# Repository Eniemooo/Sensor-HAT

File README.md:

# Sensor HAT v3 "Universal"

*Deutsch (ausführliche Anleitung): [README.de.md](README.de.md)*

An open-hardware indoor-environment sensor board, designed in KiCad 10 (65 × 56 mm, 4 layers). It runs in one of two modes, **never both at once**:

1. **HAT for Raspberry Pi** 2, 3, 4 and 5, with a HAT+ ID EEPROM and Python.
2. **Standalone** with a plug-in **Seeed Studio XIAO ESP32-S3, -C3 or -C6** (not included). It is powered over the XIAO's USB-C, runs ESPHome and shows up in Home Assistant.

> **Status:** the design is complete. KiCad ERC and DRC report no errors, and the ESPHome configs validate. **It has not been tested in hardware yet.** Build prototypes before ordering in quantity.

## What is on the board

| Function | Part | I²C address / Pi GPIO / XIAO pin |
|---|---|---|
| CO₂ (photoacoustic, not an eCO₂ estimate) | Sensirion SCD41, own 3.3 V regulator | 0x62 |
| Temperature, humidity | Sensirion SHT40 on a milled, thermally isolated island | 0x44 |
| VOC and NOx index | Sensirion SGP41 | 0x59 |
| Ambient light (lux) | Vishay VEML7700 | 0x10 |
| Sound level | TDK ICS-43434 I²S microphone | Pi GPIO18/19/20, XIAO D1/D0/D2 |
| RGB status LED (e.g. CO₂ traffic light) | WS2812B-2020 with 5 V level shifter | Pi GPIO10, XIAO D10 |
| Button | SW1 | Pi GPIO27, XIAO D4 |
| Buzzer (passive, 4 kHz) | MLT-5020 | Pi GPIO13, XIAO D3 |
| Particulate sensor port (Sensirion SEN6x/SEN5x) | J4, JST GH 6-pin, own regulator | 0x6B / 0x69 |
| mmWave radar / UART (e.g. HLK-LD2420; LD2410C with 5 V and a re-ordered cable) | J3 | Pi GPIO14/15 (+GPIO17 OUT), XIAO D6/D7 |
| 1-Wire (e.g. DS18B20) | J2 | Pi GPIO4, XIAO D5 (JP6) |
| Qwiic / STEMMA QT | J5, JST SH 4-pin | I²C, 3.3 V |
| Spare GPIOs (Pi only) | J6, 2×5 pads, not populated | GPIO5, 12, 22–26 |
| HAT ID EEPROM | onsemi CAT24C32 | ID_SD/ID_SC, 0x50 |

All parts are in active production. The one exception is the ICS-43434 microphone: it is obsolete but still widely stocked.

Two LM66100 ideal diodes keep the two power sources apart, so no current flows from the Pi into the XIAO's USB port or the other way round.

## Using it

### XIAO mode (ESPHome / Home Assistant)

1. Copy the files for your XIAO from [`software/esphome/`](software/esphome/): `sensor-hat-xiao-s3.yaml`, `-c3.yaml` or `-c6.yaml`. You always need `sensor-hat-common.yaml` and a `secrets.yaml` as well. Start from `secrets.yaml.example` and fill in:
   - your Wi-Fi name and password
   - an API encryption key (`openssl rand -base64 32`), which also protects OTA updates
   - a password for the fallback hotspot (at least 8 characters)

   The placeholders in the template are rejected by `esphome config` on purpose. With more than one board, give each its own `name:` in the substitutions, for example `sensor-hat-kitchen`.
2. Flash the XIAO once over USB **without the board attached**. Then plug it into J7/J8 with the USB-C facing outwards. Later updates go over Wi-Fi. When you add the device in Home Assistant, it asks for the API encryption key.
3. Calibrate the readings:
   - set `altitude_compensation` to your altitude
   - after 15 minutes of running, enter the SHT40 `offset` against a reference thermometer

Notes:
- **Power supply:** at least 5 V / 1.5 A with the particulate sensor and radar connected, otherwise at least 1 A. A PC USB port is not enough.
- **Battery:** do not connect a battery to the XIAO.
- **Antenna:** use a U.FL antenna. This also applies to the C6: its chip antenna sits 11 mm above the ground plane. On the C6, also set `restore_mode: ALWAYS_ON` for the `antenna_select` switch in `sensor-hat-xiao-c6.yaml` (GPIO14 high selects the U.FL socket).
- **Strapping-pin warnings:** ESPHome warns about strapping pins on the C3 (GPIO2/8/9) and the S3 (GPIO3). These pins are pulled up or not sampled on this board, so the warnings are expected and harmless.

### Raspberry Pi mode

1. Leave the XIAO socket empty.
2. Add the lines from [`software/config.txt.snippet`](software/config.txt.snippet) to `/boot/firmware/config.txt` and reboot.
3. Run [`software/sensor_test.py`](software/sensor_test.py). The pip packages it needs are listed at the top of the file.
4. To program the HAT+ ID EEPROM, see [`software/eeprom_settings.txt`](software/eeprom_settings.txt) and the German README.

### Solder jumpers: check them before you connect anything

| Jumper | As delivered | Function |
|---|---|---|
| JP1 / JP3 | open | J3 supply: JP1 = 3.3 V, JP3 = 5 V. **Never bridge both.** |
| JP4 / JP5 | JP4 closed | J4 supply: JP4 = 3.3 V for SEN6x, JP5 = 5 V for SEN5x. **5 V destroys a SEN6x.** Cut JP4, check with a multimeter that it is open, then bridge JP5. |
| JP6 | 1-2 closed | XIAO D5 = 1-Wire (J2). For the radar OUT pin, cut 1-2 and bridge 2-3. |
| JP2 | open | Bridge it to make the HAT EEPROM writable (Pi only). |

- **J3 radar:** the pin order is V+, GND, module TX, module RX, OUT.
  - HLK-LD2420 and LD2410S fit directly (bridge JP1, 3.3 V).
  - LD2410C and LD2450 need JP3 (5 V) and a re-ordered cable.
  - In ESPHome, use `sensor-hat-radar-ld2410.yaml` for the LD2410/LD2410C and the `ld2420` component for the LD2420. ESPHome has no UART support for the LD2410S, so only its OUT pin works (JP6 2-3).
- **J4 particulate sensor:** use a 6-pin JST GH cable wired pin 1 to pin 1 (VDD).
  - Check the cable with a multimeter first: crossed cables exist.
  - In XIAO mode use a SEN6x. A SEN5x needs at least 4.5 V, which is marginal on USB power.

## Ordering

[`production/`](production/) holds JLCPCB files: Gerber zip, BOM and CPL in two variants. The "komplett" variant also has JLCPCB solder the through-hole headers and XIAO sockets. The 40-pin Pi socket J1 is always soldered by hand.

Recommended settings:
- 4 layers, 1.6 mm, ENIG
- Standard PCBA, top side only, peak 245 °C
- tooling holes added by JLCPCB. The board (65 × 56 mm) is smaller than the 70 × 70 mm Standard-PCBA minimum, so it needs edge rails: on the left and right edges and one on the top edge (about 75 × 70 mm in total), never on the bottom edge with the milled sensor island. Have JLCPCB confirm this.
- **no board washing**

The complete order remark is in the German README, section "Bei JLCPCB bestellen".

Estimated landed cost per assembled board for the SMD-only variant, incl. 19 % German VAT. You buy and solder the headers J1–J3, J7 and J8 yourself. `python3 -I scripts/cost.py` recalculates it with live part prices:

| Boards | 2 | 5 | 20 | 50 | 100 |
|---|---|---|---|---|---|
| per board | ~125 € | ~77 € | ~50 € | ~42 € | ~37 € |

Small orders are expensive because of fixed setup fees, so a community group buy at cost is planned (German: [`docs/Sammelbestellung.md`](docs/Sammelbestellung.md)).

## Repository layout

| Path | Contents |
|---|---|
| `Sensor-HAT.kicad_pro/.kicad_sch/.kicad_pcb` | KiCad 10 project |
| `production/` | Gerber, BOM, CPL for JLCPCB |
| `docs/` | schematic and assembly PDFs, renders, group-buy documents (German) |
| `software/` | ESPHome configs, Pi config, test script, EEPROM settings |
| `lib/` | project symbols and footprints (3D models: see below) |
| `scripts/` | the generator: `design.py` (parts and nets) and `placement.py` are the single source of truth; `build.sh` regenerates schematic and board and autoroutes them |

## Building from source

```bash
pip install easyeda2kicad
python3 -I scripts/fetch_3d_models.py .   # LCSC 3D models, only needed for 3D view, renders, STEP
export FREEROUTING_JAR=/path/to/freerouting-2.5.0.jar
scripts/build.sh                          # schematic + ERC, board, autorouting, GND repair, DRC
python3 -I scripts/export.py .            # Gerber, BOM, CPL, PDFs, renders, STEP
```

Requirements:
- KiCad 10
- Java
- [Freerouting](https://github.com/freerouting/freerouting) 2.5

The scripts expect KiCad on macOS at `~/Applications/KiCad/KiCad.app`. For other installations, change the paths at the top of `build.sh`, `kicadlib.py`, `gen_pcb.py`, `route.py`, `cleanup.py` and `export.py`. If your Java is not Homebrew's openjdk, run `export JAVA=$(which java)` before `build.sh`.

## Licence

- Hardware (KiCad project, `scripts/design.py` and `scripts/placement.py`, production files, PDFs, renders): [CERN-OHL-S-2.0](LICENSES/CERN-OHL-S-2.0.txt)
- Software and the other scripts: [MIT](LICENSES/MIT.txt)
- Documentation: [CC-BY-SA-4.0](LICENSES/CC-BY-SA-4.0.txt) or, at your choice, [CERN-OHL-S-2.0](LICENSES/CERN-OHL-S-2.0.txt)

Source: <https://github.com/Eniemooo/Sensor-HAT>. Which licence covers which file is listed in [LICENSE.md](LICENSE.md). Some symbols and footprints come from the LCSC/EasyEDA library, which has no licence of its own. These parts, and the trademarks, are listed in [NOTICE.md](NOTICE.md).

Raspberry Pi is a trademark of Raspberry Pi Ltd. This project is not affiliated with Raspberry Pi Ltd or Seeed Studio. No warranty.

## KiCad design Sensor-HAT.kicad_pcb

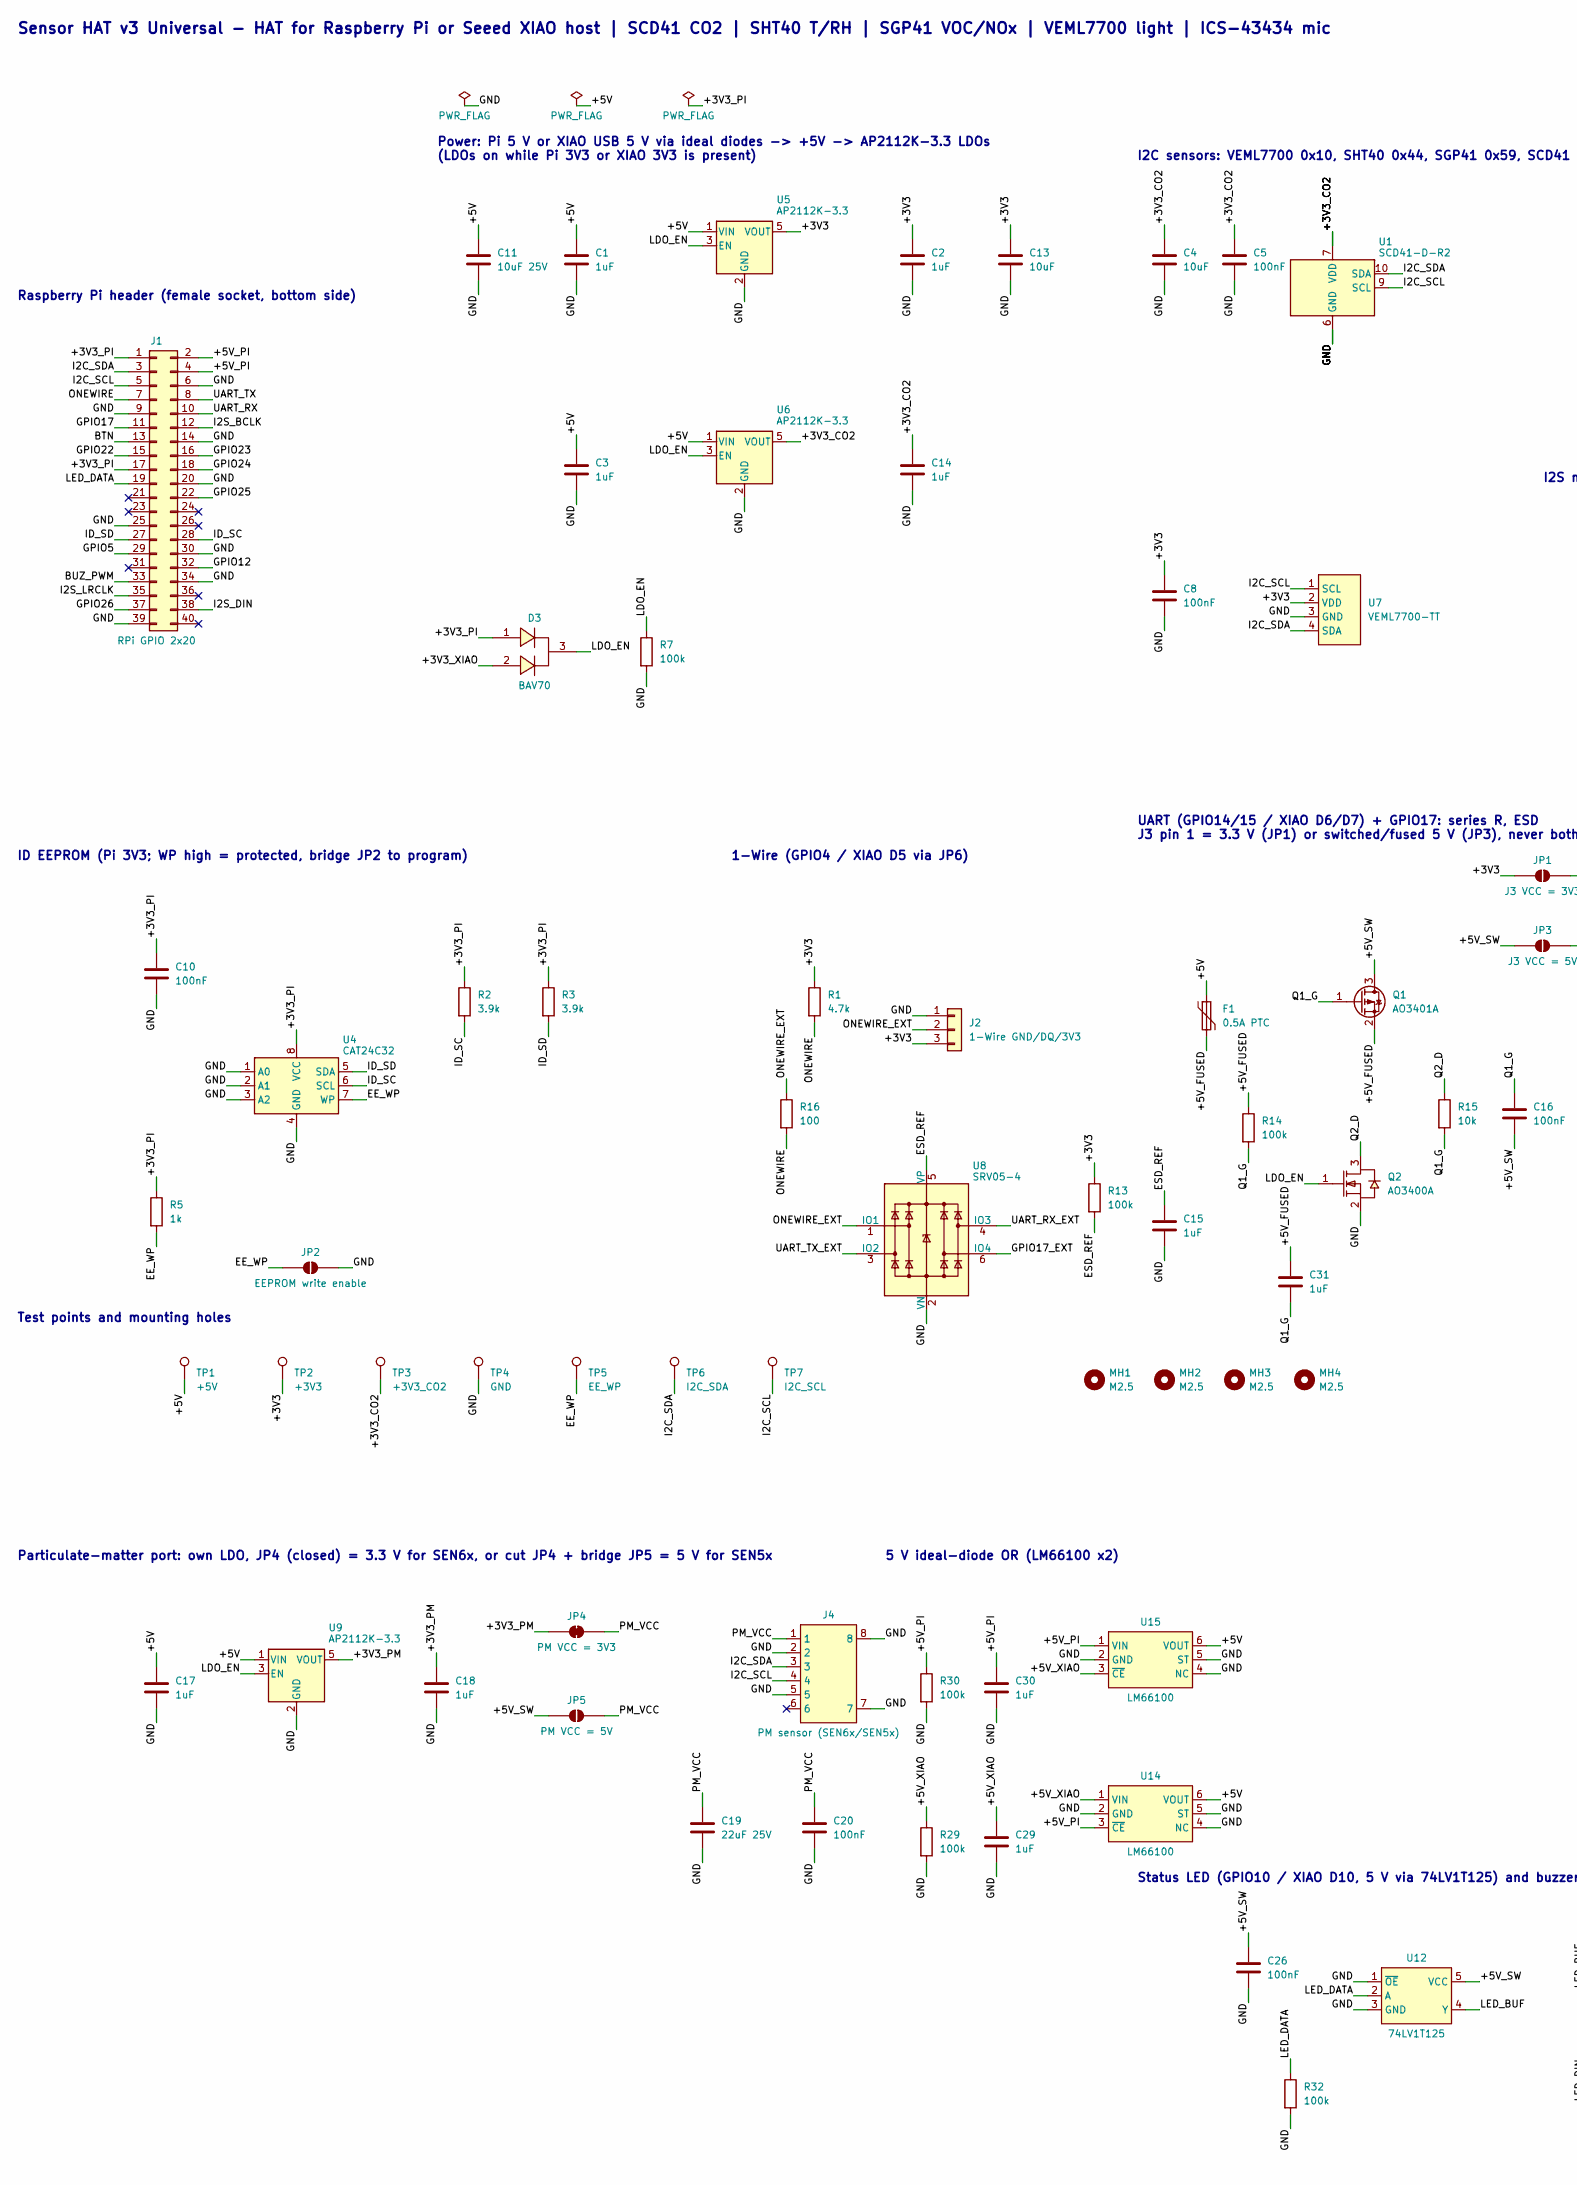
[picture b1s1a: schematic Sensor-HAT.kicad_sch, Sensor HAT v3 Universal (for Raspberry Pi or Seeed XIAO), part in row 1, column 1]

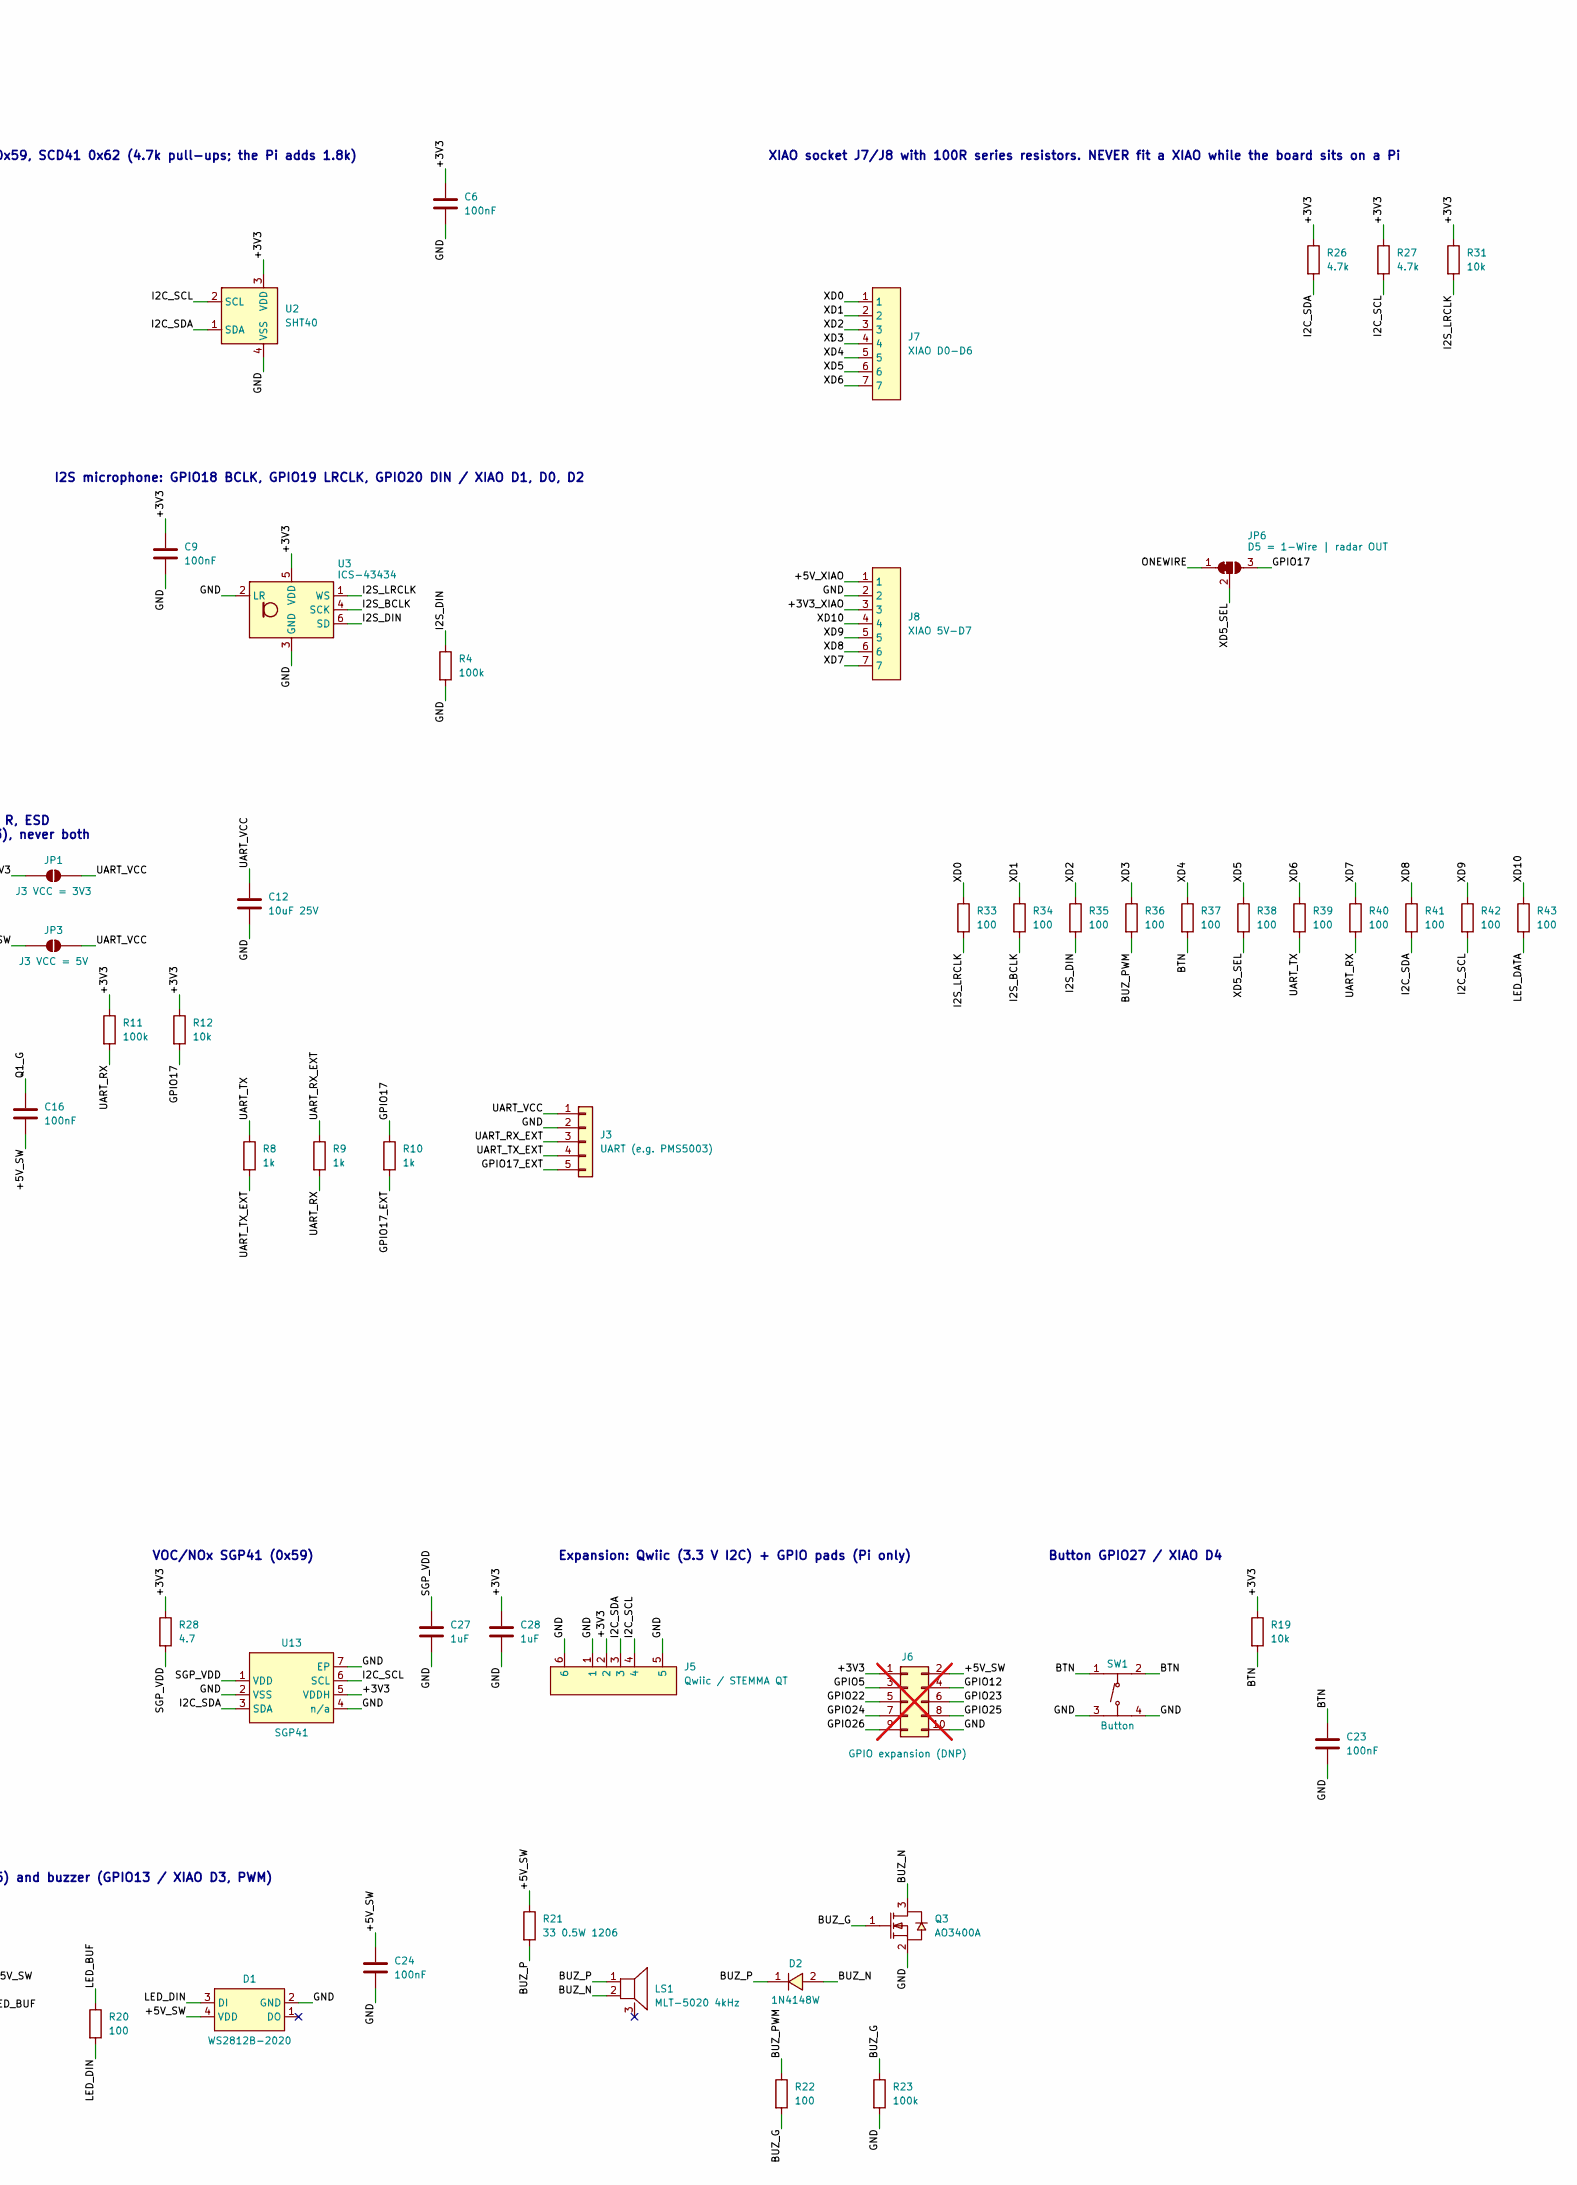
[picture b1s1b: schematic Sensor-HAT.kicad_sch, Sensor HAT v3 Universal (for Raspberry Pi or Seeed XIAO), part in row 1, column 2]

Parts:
C1, C2, C3, C14, C15, C17, C18, C27, C28, C29, C30, C31: 1uF; C_0603_1608Metric; MPN CL10A105KB8NNNC; LCSC C15849
C4, C13: 10uF; C_0603_1608Metric; MPN CL10A106KP8NNNC; LCSC C19702
C5, C6, C8, C9, C10, C16, C20, C23, C24, C26: 100nF; C_0603_1608Metric; MPN CC0603KRX7R9BB104; LCSC C14663
C11, C12: 10uF 25V; C_0805_2012Metric; MPN CL21A106KAYNNNE; LCSC C15850
C19: 22uF 25V; C_0805_2012Metric; MPN CL21A226MAQNNNE; LCSC C45783
D1: WS2812B-2020; LED-SMD_4P-L2.2-W2.0-P1.00_WS2815C-2020-4P; MPN WS2812B-2020-V6; LCSC C52917434
D2: 1N4148W; SOD-123F_L2.7-W1.6-LS3.8-RD; MPN 1N4148W; LCSC C81598
D3: BAV70; SOT-23-3_L3.0-W1.7-P0.95-LS2.9-BR; MPN BAV70; LCSC C68978
F1: 0.5A PTC; Fuse_1206_3216Metric; MPN nSMD050-33V; LCSC C70077
J1: RPi GPIO 2x20; PinSocket_2x20_P2.54mm_Vertical; MPN 2.54-2*20; LCSC C2977589
J2: 1-Wire GND/DQ/3V3; PinHeader_1x03_P2.54mm_Vertical; MPN 2.54-1*3P; LCSC C49257
J3: UART (e.g. PMS5003); PinHeader_1x05_P2.54mm_Vertical; MPN HX PZ2.54-1x5P ZZ; LCSC C32713271
J4: PM sensor (SEN6x/SEN5x); CONN-SMD_6P-P1.25_BM06B-GHS-TBT-LF-SN-N; MPN BM06B-GHS-TBT(LF)(SN); LCSC C189892
J5: Qwiic / STEMMA QT; CONN-SMD_BM04B-SRSS-TB; MPN BM04B-SRSS-TB(LF)(SN); LCSC C160390
J6: GPIO expansion (DNP); PinHeader_2x05_P2.54mm_Vertical; not fitted
J7: XIAO D0-D6; HDR-TH_7P-P2.54-V-F; MPN PM254-1-07-Z-8.5; LCSC C2897370
J8: XIAO 5V-D7; HDR-TH_7P-P2.54-V-F; MPN PM254-1-07-Z-8.5; LCSC C2897370
JP1: J3 VCC = 3V3; SolderJumper-2_P1.3mm_Open_RoundedPad1.0x1.5mm
JP2: EEPROM write enable; SolderJumper-2_P1.3mm_Open_RoundedPad1.0x1.5mm
JP3: J3 VCC = 5V; SolderJumper-2_P1.3mm_Open_RoundedPad1.0x1.5mm
JP4: PM VCC = 3V3; SolderJumper-2_P1.3mm_Bridged_RoundedPad1.0x1.5mm
JP5: PM VCC = 5V; SolderJumper-2_P1.3mm_Open_RoundedPad1.0x1.5mm
JP6: D5 = 1-Wire | radar OUT; SolderJumper-3_P1.3mm_Bridged12_RoundedPad1.0x1.5mm
LS1: MLT-5020 4kHz; BUZ-SMD_L5.0-W5.5-P4.60; MPN MLT-5020; LCSC C94598
MH1, MH2, MH3, MH4: M2.5; MountingHole_2.7mm_M2.5
Q1: AO3401A; SOT-23_L2.9-W1.3-P1.90-LS2.4-BR; MPN AO3401A; LCSC C15127
Q2, Q3: AO3400A; SOT-23_L2.9-W1.3-P1.90-LS2.4-BR; MPN AO3400A; LCSC C20917
R1, R26, R27: 4.7k; R_0603_1608Metric; MPN 0603WAF4701T5E; LCSC C23162
R2, R3: 3.9k; R_0603_1608Metric; MPN 0603WAF3901T5E; LCSC C23018
R4, R7, R11, R13, R14, R23, R29, R30, R32: 100k; R_0603_1608Metric; MPN 0603WAF1003T5E; LCSC C25803
R5, R8, R9, R10: 1k; R_0603_1608Metric; MPN 0603WAF1001T5E; LCSC C21190
R12, R15, R19, R31: 10k; R_0603_1608Metric; MPN 0603WAF1002T5E; LCSC C25804
R16, R20, R22, R33, R34, R35, R36, R37, R38, R39, R40, R41, R42, R43: 100; R_0603_1608Metric; MPN 0603WAF1000T5E; LCSC C22775
R21: 33 0.5W 1206; R_1206_3216Metric; MPN FRP1206F33R0TS; LCSC C5713420
R28: 4.7; R_0603_1608Metric; MPN 0603WAF470KT5E; LCSC C23164
SW1: Button; SW-SMD_4P-L5.1-W5.1-P3.70-LS6.5-TL_H1.5; MPN TS-1187A-B-A-B; LCSC C318884
TP1: +5V; TestPoint_Pad_D1.5mm
TP2: +3V3; TestPoint_Pad_D1.5mm
TP3: +3V3_CO2; TestPoint_Pad_D1.5mm
TP4: GND; TestPoint_Pad_D1.5mm
TP5: EE_WP; TestPoint_Pad_D1.5mm
TP6: I2C_SDA; TestPoint_Pad_D1.5mm
TP7: I2C_SCL; TestPoint_Pad_D1.5mm
U1: SCD41-D-R2; LGA-20_L10.1-W10.1-P1.25-TL_SCD41-D-R2; MPN SCD41-D-R2; LCSC C3659294
U2: SHT40; SHT4x_DFN-4_1.5x1.5mm_P0.8mm_NoCentralPad; MPN SHT40-AD1B-R2; LCSC C2909890
U3: ICS-43434; InvenSense_ICS-43434-6_3.5x2.65mm; MPN ICS-43434; LCSC C5656610
U4: CAT24C32; SOIC-8_L5.0-W4.0-P1.27-LS6.0-BL; MPN CAT24C32WI-GT3; LCSC C81193
U5, U6, U9: AP2112K-3.3; SOT-25-5_L2.9-W1.6-P0.95-LS2.8-BL; MPN AP2112K-3.3TRG1; LCSC C51118
U7: VEML7700-TT; SENSOR-SMD_EML7700-TT; MPN VEML7700-TT; LCSC C1850416
U8: SRV05-4; SOT-23-6_L2.9-W1.6-P0.95-LS2.8-BR; MPN SRV05-4-P-T7; LCSC C85364
U12: 74LV1T125; SOT-23-5_L3.0-W1.7-P0.95-LS2.8-BL; MPN SN74LV1T125DBVR; LCSC C473338
U13: SGP41; DFN-6_L2.4-W2.4-P0.80-TL-EP; MPN SGP41-D-R4; LCSC C3659325
U14, U15: LM66100; SC-70-6_L2.0-W1.3-P0.65-LS2.1-BL; MPN LM66100DCKR; LCSC C2869734

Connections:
/+3V3: C2.1, C6.1, C8.1, C9.1, C13.1, C28.1, J2.3, J5.2, J6.1, JP1.1 (A), R1.1, R11.1, R12.1, R13.1, R19.1, R26.1, R27.1, R28.1, R31.1, TP2.1, U2.3 (VDD), U3.5 (VDD), U5.5 (VOUT), U7.2 (VDD), U13.5 (VDDH)
/+3V3_CO2: C4.1, C5.1, C14.1, TP3.1, U1.7 (VDD), U1.19 (VDD), U6.5 (VOUT)
/+3V3_PI: C10.1, D3.1, J1.1, J1.17, R2.1, R3.1, R5.1, U4.8 (VCC)
/+3V3_PM: C18.1, JP4.1 (A), U9.5 (VOUT)
/+3V3_XIAO: D3.2, J8.3
/+5V: C1.1, C3.1, C11.1, C17.1, F1.1, TP1.1, U5.1 (VIN), U6.1 (VIN), U9.1 (VIN), U14.6 (VOUT), U15.6 (VOUT)
/+5V_FUSED: C31.1, F1.2, Q1.2 (S), R14.1
/+5V_PI: C30.1, J1.2, J1.4, R30.1, U14.3 (~CE), U15.1 (VIN)
/+5V_SW: C16.2, C24.1, C26.1, D1.4 (VDD), J6.2, JP3.1 (A), JP5.1 (A), Q1.3 (D), R21.1, U12.5 (VCC)
/+5V_XIAO: C29.1, J8.1, R29.1, U14.1 (VIN), U15.3 (~CE)
/BTN: C23.1, J1.13, R19.2, R37.2, SW1.1 (A), SW1.2 (B)
/BUZ_G: Q3.1 (G), R22.2, R23.1
/BUZ_N: D2.2 (A), LS1.2 (-), Q3.3 (D)
/BUZ_P: D2.1 (K), LS1.1 (+), R21.2
/BUZ_PWM: J1.33, R22.1, R36.2
/EE_WP: JP2.1 (A), R5.2, TP5.1, U4.7 (WP)
/ESD_REF: C15.1, R13.2, U8.5 (VP)
/GND: C1.2, C2.2, C3.2, C4.2, C5.2, C6.2, C8.2, C9.2, C10.2, C11.2, C12.2, C13.2, C14.2, C15.2, C17.2, C18.2, C19.2, C20.2, C23.2, C24.2, C26.2, C27.2, C28.2, C29.2, C30.2, D1.2 (GND), J1.6, J1.9, J1.14, J1.20, J1.25, J1.30, J1.34, J1.39, J2.1, J3.2, J4.2, J4.5, J4.7, J4.8, J5.1, J5.5, J5.6, J6.10, J8.2, JP2.2 (B), Q2.2 (S), Q3.2 (S), R4.2, R7.2, R23.2, R29.2, R30.2, R32.2, SW1.3 (C), SW1.4 (D), TP4.1, U1.6 (GND), U1.20 (GND), U1.21 (GND), U2.4 (VSS), U3.2 (LR), U3.3 (GND), U4.1 (A0), U4.2 (A1), U4.3 (A2), U4.4 (GND), U5.2 (GND), U6.2 (GND), U7.3 (GND), U8.2 (VN), U9.2 (GND), U12.1 (~OE), U12.3 (GND), U13.2 (VSS), U13.4 (n/a), U13.7 (EP), U14.2 (GND), U14.4 (NC), U14.5 (ST), U15.2 (GND), U15.4 (NC), U15.5 (ST)
/GPIO5: J1.29, J6.3
/GPIO12: J1.32, J6.4
/GPIO17: J1.11, JP6.3 (B), R10.1, R12.2
/GPIO17_EXT: J3.5, R10.2, U8.6 (IO4)
/GPIO22: J1.15, J6.5
/GPIO23: J1.16, J6.6
/GPIO24: J1.18, J6.7
/GPIO25: J1.22, J6.8
/GPIO26: J1.37, J6.9
/I2C_SCL: J1.5, J4.4, J5.4, R27.2, R42.2, TP7.1, U1.9 (SCL), U2.2 (SCL), U7.1 (SCL), U13.6 (SCL)
/I2C_SDA: J1.3, J4.3, J5.3, R26.2, R41.2, TP6.1, U1.10 (SDA), U2.1 (SDA), U7.4 (SDA), U13.3 (SDA)
/I2S_BCLK: J1.12, R34.2, U3.4 (SCK)
/I2S_DIN: J1.38, R4.1, R35.2, U3.6 (SD)
/I2S_LRCLK: J1.35, R31.2, R33.2, U3.1 (WS)
/ID_SC: J1.28, R2.2, U4.6 (SCL)
/ID_SD: J1.27, R3.2, U4.5 (SDA)
/LDO_EN: D3.3, Q2.1 (G), R7.1, U5.3 (EN), U6.3 (EN), U9.3 (EN)
/LED_BUF: R20.1, U12.4 (Y)
/LED_DATA: J1.19, R32.1, R43.2, U12.2 (A)
/LED_DIN: D1.3 (DI), R20.2
/ONEWIRE: J1.7, JP6.1 (A), R1.2, R16.2
/ONEWIRE_EXT: J2.2, R16.1, U8.1 (IO1)
/PM_VCC: C19.1, C20.1, J4.1, JP4.2 (B), JP5.2 (B)
/Q1_G: C16.1, C31.2, Q1.1 (G), R14.2, R15.2
/Q2_D: Q2.3 (D), R15.1
/SGP_VDD: C27.1, R28.2, U13.1 (VDD)
/UART_RX: J1.10, R9.2, R11.2, R40.2
/UART_RX_EXT: J3.3, R9.1, U8.4 (IO3)
/UART_TX: J1.8, R8.1, R39.2
/UART_TX_EXT: J3.4, R8.2, U8.3 (IO2)
/UART_VCC: C12.1, J3.1, JP1.2 (B), JP3.2 (B)
/XD0: J7.1, R33.1
/XD1: J7.2, R34.1
/XD2: J7.3, R35.1
/XD3: J7.4, R36.1
/XD4: J7.5, R37.1
/XD5: J7.6, R38.1
/XD5_SEL: JP6.2 (C), R38.2
/XD6: J7.7, R39.1
/XD7: J8.7, R40.1
/XD8: J8.6, R41.1
/XD9: J8.5, R42.1
/XD10: J8.4, R43.1

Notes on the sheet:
Sensor HAT v3 Universal - HAT for Raspberry Pi or Seeed XIAO host | SCD41 CO2 | SHT40 T/RH | SGP41 VOC/NOx | VEML7700 light | ICS-43434 mic
Raspberry Pi header (female socket, bottom side)
Power: Pi 5 V or XIAO USB 5 V via ideal diodes -> +5V -> AP2112K-3.3 LDOs
(LDOs on while Pi 3V3 or XIAO 3V3 is present)
I2C sensors: VEML7700 0x10, SHT40 0x44, SGP41 0x59, SCD41 0x62 (4.7k pull-ups; the Pi adds 1.8k)
I2S microphone: GPIO18 BCLK, GPIO19 LRCLK, GPIO20 DIN / XIAO D1, D0, D2
XIAO socket J7/J8 with 100R series resistors. NEVER fit a XIAO while the board sits on a Pi
ID EEPROM (Pi 3V3; WP high = protected, bridge JP2 to program)
1-Wire (GPIO4 / XIAO D5 via JP6)
UART (GPIO14/15 / XIAO D6/D7) + GPIO17: series R, ESD
J3 pin 1 = 3.3 V (JP1) or switched/fused 5 V (JP3), never both
Test points and mounting holes
Particulate-matter port: own LDO, JP4 (closed) = 3.3 V for SEN6x, or cut JP4 + bridge JP5 = 5 V for SEN5x
5 V ideal-diode OR (LM66100 x2)
VOC/NOx SGP41 (0x59)
Expansion: Qwiic (3.3 V I2C) + GPIO pads (Pi only)
Button GPIO27 / XIAO D4
Status LED (GPIO10 / XIAO D10, 5 V via 74LV1T125) and buzzer (GPIO13 / XIAO D3, PWM)

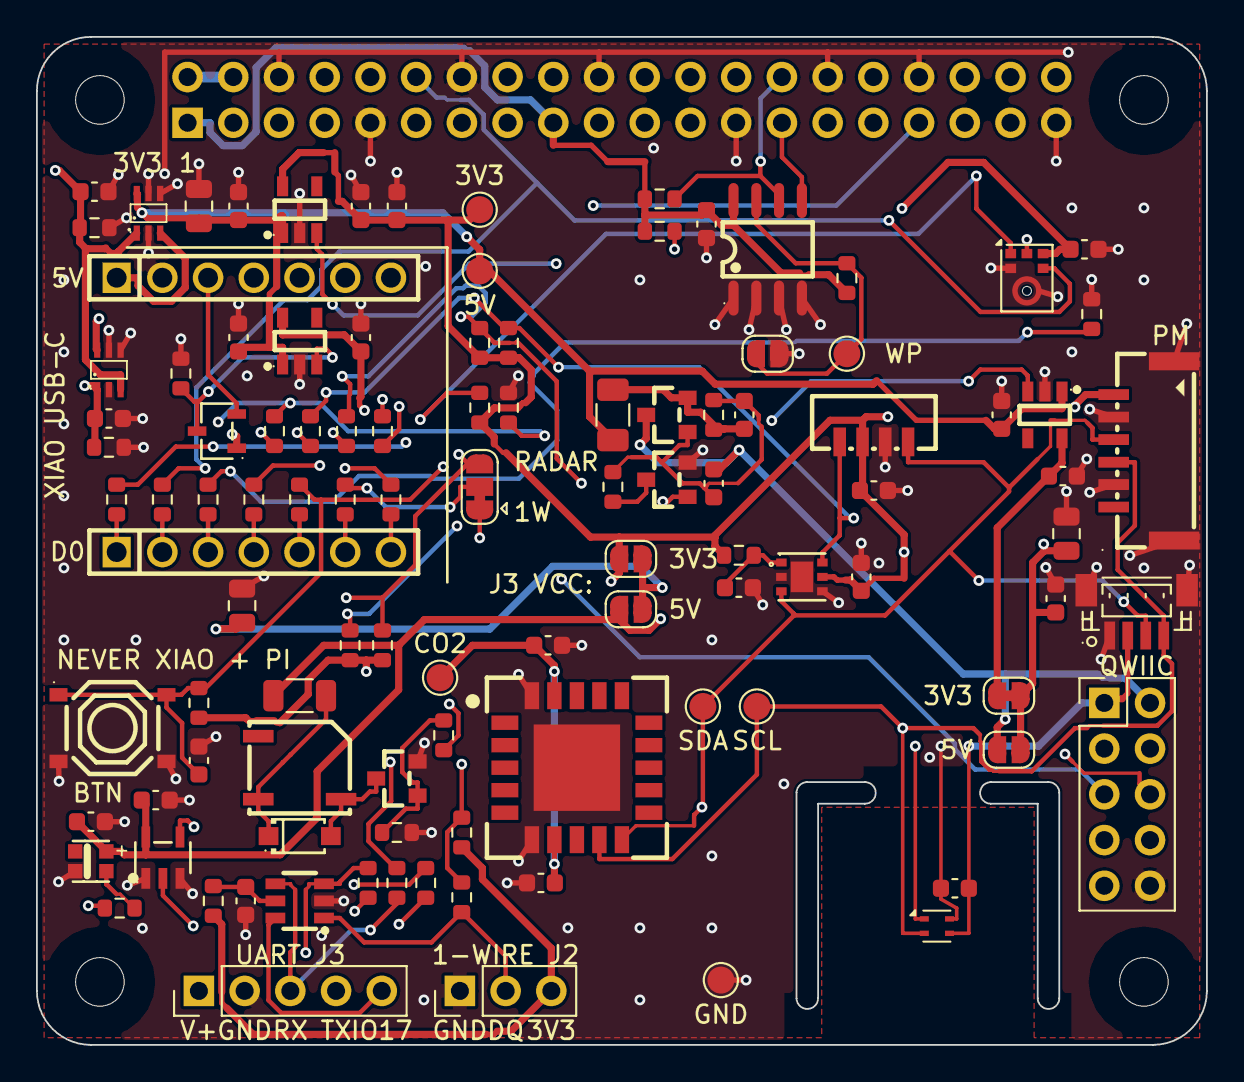
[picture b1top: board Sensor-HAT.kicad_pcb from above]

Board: 4 copper layers, 65.0 x 56.0 mm, 112 parts (1 on the bottom side), 61 nets.

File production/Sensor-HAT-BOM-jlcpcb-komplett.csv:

Comment,Designator,Footprint,LCSC Part #,Quantity,Manufacturer,MPN
AP2112K-3.3,"U5,U6,U9",SOT-25-5_L2.9-W1.6-P0.95-LS2.8-BL,C51118,3,Diodes,AP2112K-3.3TRG1
10uF 25V,"C11,C12",C_0805_2012Metric,C15850,2,Samsung,CL21A106KAYNNNE
1uF,"C1,C2,C3,C14,C15,C17,C18,C27,C28,C29,C30,C31",C_0603_1608Metric,C15849,12,Samsung,CL10A105KB8NNNC
10uF,"C4,C13",C_0603_1608Metric,C19702,2,Samsung,CL10A106KP8NNNC
BAV70,D3,SOT-23-3_L3.0-W1.7-P0.95-LS2.9-BR,C68978,1,CJ,BAV70
LM66100,"U14,U15",SC-70-6_L2.0-W1.3-P0.65-LS2.1-BL,C2869734,2,TI,LM66100DCKR
100k,"R4,R7,R11,R13,R14,R23,R29,R30,R32",R_0603_1608Metric,C25803,9,UNI-ROYAL,0603WAF1003T5E
SCD41-D-R2,U1,LGA-20_L10.1-W10.1-P1.25-TL_SCD41-D-R2,C3659294,1,Sensirion,SCD41-D-R2
100nF,"C5,C6,C8,C9,C10,C16,C20,C23,C24,C26",C_0603_1608Metric,C14663,10,YAGEO,CC0603KRX7R9BB104
SHT40,U2,SHT4x_DFN-4_1.5x1.5mm_P0.8mm_NoCentralPad,C2909890,1,Sensirion,SHT40-AD1B-R2
SGP41,U13,DFN-6_L2.4-W2.4-P0.80-TL-EP,C3659325,1,Sensirion,SGP41-D-R4
4.7,R28,R_0603_1608Metric,C23164,1,UNI-ROYAL,0603WAF470KT5E
VEML7700-TT,U7,SENSOR-SMD_EML7700-TT,C1850416,1,Vishay,VEML7700-TT
ICS-43434,U3,InvenSense_ICS-43434-6_3.5x2.65mm,C5656610,1,TDK InvenSense,ICS-43434
CAT24C32,U4,SOIC-8_L5.0-W4.0-P1.27-LS6.0-BL,C81193,1,onsemi,CAT24C32WI-GT3
3.9k,"R2,R3",R_0603_1608Metric,C23018,2,UNI-ROYAL,0603WAF3901T5E
1k,"R5,R8,R9,R10",R_0603_1608Metric,C21190,4,UNI-ROYAL,0603WAF1001T5E
1-Wire GND/DQ/3V3,J2,PinHeader_1x03_P2.54mm_Vertical,C49257,1,BOOMELE,2.54-1*3P
4.7k,"R1,R26,R27",R_0603_1608Metric,C23162,3,UNI-ROYAL,0603WAF4701T5E
100,"R16,R20,R22,R33,R34,R35,R36,R37,R38,R39,R40,R41,R42,R43",R_0603_1608Metric,C22775,14,UNI-ROYAL,0603WAF1000T5E
UART (e.g. PMS5003),J3,PinHeader_1x05_P2.54mm_Vertical,C32713271,1,hanxia,HX PZ2.54-1x5P ZZ
10k,"R12,R15,R19,R31",R_0603_1608Metric,C25804,4,UNI-ROYAL,0603WAF1002T5E
SRV05-4,U8,SOT-23-6_L2.9-W1.6-P0.95-LS2.8-BR,C85364,1,ProTek Devices,SRV05-4-P-T7
0.5A PTC,F1,Fuse_1206_3216Metric,C70077,1,TECHFUSE,nSMD050-33V
AO3401A,Q1,SOT-23_L2.9-W1.3-P1.90-LS2.4-BR,C15127,1,Alpha & Omega,AO3401A
AO3400A,"Q2,Q3",SOT-23_L2.9-W1.3-P1.90-LS2.4-BR,C20917,2,Alpha & Omega,AO3400A
22uF 25V,C19,C_0805_2012Metric,C45783,1,Samsung,CL21A226MAQNNNE
PM sensor (SEN6x/SEN5x),J4,CONN-SMD_6P-P1.25_BM06B-GHS-TBT-LF-SN-N,C189892,1,JST,BM06B-GHS-TBT(LF)(SN)
Qwiic / STEMMA QT,J5,CONN-SMD_BM04B-SRSS-TB,C160390,1,JST,BM04B-SRSS-TB(LF)(SN)
Button,SW1,SW-SMD_4P-L5.1-W5.1-P3.70-LS6.5-TL_H1.5,C318884,1,XKB,TS-1187A-B-A-B
74LV1T125,U12,SOT-23-5_L3.0-W1.7-P0.95-LS2.8-BL,C473338,1,TI,SN74LV1T125DBVR
WS2812B-2020,D1,LED-SMD_4P-L2.2-W2.0-P1.00_WS2815C-2020-4P,C52917434,1,Worldsemi,WS2812B-2020-V6
MLT-5020 4kHz,LS1,BUZ-SMD_L5.0-W5.5-P4.60,C94598,1,Huaneng,MLT-5020
33 0.5W 1206,R21,R_1206_3216Metric,C5713420,1,FOJAN,FRP1206F33R0TS
1N4148W,D2,SOD-123F_L2.7-W1.6-LS3.8-RD,C81598,1,ST,1N4148W
XIAO D0-D6,"J7,J8",HDR-TH_7P-P2.54-V-F,C2897370,2,HCTL,PM254-1-07-Z-8.5

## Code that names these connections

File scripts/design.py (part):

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    "2": "+5V_PI", "4": "+5V_PI",
    "3": "I2C_SDA", "5": "I2C_SCL",
    "7": "ONEWIRE",
    "8": "UART_TX", "10": "UART_RX", "11": "GPIO17",
    "12": "I2S_BCLK", "35": "I2S_LRCLK", "38": "I2S_DIN",
    "27": "ID_SD", "28": "ID_SC",
    # user interface
    "13": "BTN",          # GPIO27  push-button
    "19": "LED_DATA",     # GPIO10  SPI0 MOSI -> WS2812 status LED
    "33": "BUZ_PWM",      # GPIO13  PWM1 -> buzzer
    # spare GPIOs on the J6 expansion pads
    "29": "GPIO5", "32": "GPIO12", "15": "GPIO22", "16": "GPIO23",
    "18": "GPIO24", "22": "GPIO25", "37": "GPIO26",
}
for _p in ("6", "9", "14", "20", "25", "30", "34", "39"):
    J1_PINS[_p] = "GND"
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    dict(ref="U5", sym="Regulator_Linear:AP2112K-3.3", value="AP2112K-3.3",
         fp="SensorHAT:SOT-25-5_L2.9-W1.6-P0.95-LS2.8-BL",
         LCSC="C51118", MPN="AP2112K-3.3TRG1", Manufacturer="Diodes",
         pins={"1": "+5V", "2": "GND", "3": "LDO_EN", "5": "+3V3"}, sch=(157.48, 58.42),
         desc="3.3 V LDO for SHT40, SGP41, VEML7700, mic, pull-ups, Qwiic, 1-Wire, UART"),
    dict(ref="U6", sym="Regulator_Linear:AP2112K-3.3", value="AP2112K-3.3",
         fp="SensorHAT:SOT-25-5_L2.9-W1.6-P0.95-LS2.8-BL",
         LCSC="C51118", MPN="AP2112K-3.3TRG1", Manufacturer="Diodes",
         pins={"1": "+5V", "2": "GND", "3": "LDO_EN", "5": "+3V3_CO2"}, sch=(157.48, 96.52),
         desc="Separate 3.3 V LDO for SCD41 (Sensirion recommendation)"),
    C10u25("C11", "+5V", (109.22, 60.96), desc="5 V bulk at header"),
    C1u("C1", "+5V", (127.0, 60.96), desc="U5 input"),
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    C1u("C14", "+3V3_CO2", (187.96, 99.06), desc="U6 output"),
    dict(ref="D3", sym="SensorHAT:BAV70-C68978", value="BAV70", fp="SensorHAT:SOT-23-3_L3.0-W1.7-P0.95-LS2.9-BR",
         LCSC="C68978", MPN="BAV70", Manufacturer="CJ",
         pins={"1": "+3V3_PI", "2": "+3V3_XIAO", "3": "LDO_EN"}, sch=(119.38, 132.08),
         desc="Enable OR: LDOs and 5 V switch on while the Pi 3V3 OR the XIAO 3V3 is up (HAT+ standby kept)"),
    # 5 V: TI dual ideal-diode ORing (LM66100 datasheet 9.2.1), each CE on the other source
    dict(ref="U15", sym="SensorHAT:LM66100DCKR", value="LM66100", fp="SensorHAT:SC-70-6_L2.0-W1.3-P0.65-LS2.1-BL",
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    dict(ref="U2", sym="Sensor_Humidity:SHT4x", value="SHT40",
         fp="SensorHAT:SHT4x_DFN-4_1.5x1.5mm_P0.8mm_NoCentralPad",
         LCSC="C2909890", MPN="SHT40-AD1B-R2", Manufacturer="Sensirion",
         pins={"1": "I2C_SDA", "2": "I2C_SCL", "3": "+3V3", "4": "GND"},
         sch=(337.82, 71.12), desc="Temperature/humidity on the milled island, I2C 0x44 (no copper under the die)"),
    C100n("C6", "+3V3", (373.38, 50.8), desc="SHT40 VDD"),
    dict(ref="U13", sym="SensorHAT:SGP41-D-R4", value="SGP41",
         fp="SensorHAT:DFN-6_L2.4-W2.4-P0.80-TL-EP",
         LCSC="C3659325", MPN="SGP41-D-R4", Manufacturer="Sensirion",
         pins={"1": "SGP_VDD", "2": "GND", "3": "I2C_SDA", "4": "GND", "5": "+3V3", "6": "I2C_SCL", "7": "GND"},
         sch=(345.44, 320.04), desc="VOC + NOx index (open gas-index algorithm), I2C 0x59"),
    R("R28", "4.7", "+3V3", "SGP_VDD", "C23164", "0603WAF470KT5E", (322.58, 309.88),
      desc="SGP41 VDD RC filter (datasheet Fig. 6)"),
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    dict(ref="U7", sym="SensorHAT:VEML7700-TT", value="VEML7700-TT",
         fp="SensorHAT:SENSOR-SMD_EML7700-TT",
         LCSC="C1850416", MPN="VEML7700-TT", Manufacturer="Vishay",
         pins={"1": "I2C_SCL", "2": "+3V3", "3": "GND", "4": "I2C_SDA"},
         sch=(264.16, 124.46), desc="Ambient light sensor (top view), I2C 0x10"),
    C100n("C8", "+3V3", (233.68, 121.92), desc="VEML7700 VDD"),

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    dict(ref="U3", sym="Sensor_Audio:ICS-43434", value="ICS-43434",
         fp="Sensor_Audio:InvenSense_ICS-43434-6_3.5x2.65mm",
         LCSC="C5656610", MPN="ICS-43434", Manufacturer="TDK InvenSense",
         pins={"1": "I2S_LRCLK", "2": "GND", "3": "GND", "4": "I2S_BCLK", "5": "+3V3", "6": "I2S_DIN"},
         sch=(345.44, 124.46), jlc_rot=-90,
         desc="I2S MEMS microphone (bottom port), left channel"),
    C100n("C9", "+3V3", (322.58, 114.3), desc="Mic VDD"),
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    dict(ref="U4", sym="Memory_EEPROM:24LC32", value="CAT24C32",
         fp="SensorHAT:SOIC-8_L5.0-W4.0-P1.27-LS6.0-BL",
         LCSC="C81193", MPN="CAT24C32WI-GT3", Manufacturer="onsemi",
         pins={"1": "GND", "2": "GND", "3": "GND", "4": "GND", "5": "ID_SD", "6": "ID_SC",
               "7": "EE_WP", "8": "+3V3_PI"},
         sch=(76.2, 210.82), desc="HAT+ ID EEPROM, address 0x50 on ID_SD/ID_SC"),
    C100n("C10", "+3V3_PI", (50.8, 190.5), desc="EEPROM VCC"),
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    R("R5", "1k", "+3V3_PI", "EE_WP", "C21190", "0603WAF1001T5E", (50.8, 233.68), desc="WP pull-up = write protected"),
    dict(ref="JP2", sym="Jumper:SolderJumper_2_Open", value="EEPROM write enable",
         fp="Jumper:SolderJumper-2_P1.3mm_Open_RoundedPad1.0x1.5mm",
         pins={"1": "EE_WP", "2": "GND"}, sch=(78.74, 243.84), no_bom=True,
         desc="Bridge to allow writing the ID EEPROM"),

    # ---------------- 1-Wire ----------------
    dict(ref="J2", sym="Connector_Generic:Conn_01x03", value="1-Wire GND/DQ/3V3",
         fp="Connector_PinHeader_2.54mm:PinHeader_1x03_P2.54mm_Vertical",
         LCSC="C49257", MPN="2.54-1*3P", Manufacturer="BOOMELE", hand=True, jlc_rot=-90,
         pins={"1": "GND", "2": "ONEWIRE_EXT", "3": "+3V3"}, sch=(195.58, 200.66),
         desc="DS18B20 header, same pin order as the TO-92 package (GND, DQ, VDD)"),
    R("R1", "4.7k", "+3V3", "ONEWIRE", "C23162", "0603WAF4701T5E", (170.18, 195.58), desc="1-Wire pull-up"),
    R("R16", "100", "ONEWIRE_EXT", "ONEWIRE", "C22775", "0603WAF1000T5E", (165.1, 215.9),
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    dict(ref="J3", sym="Connector_Generic:Conn_01x05", value="UART (e.g. PMS5003)",
         fp="Connector_PinHeader_2.54mm:PinHeader_1x05_P2.54mm_Vertical",
         LCSC="C32713271", MPN="HX PZ2.54-1x5P ZZ", Manufacturer="hanxia", hand=True, jlc_rot=-90,
         pins={"1": "UART_VCC", "2": "GND", "3": "UART_RX_EXT", "4": "UART_TX_EXT", "5": "GPIO17_EXT"},
         sch=(398.78, 220.98),
         desc="1 V+ (JP1 3.3 V or JP3 5 V) 2 GND 3 RX of Pi (to device TX) 4 TX of Pi (to device RX) 5 GPIO17"),
    R("R8", "1k", "UART_TX", "UART_TX_EXT", "C21190", "0603WAF1001T5E", (337.82, 223.52), desc="series, Pi TXD"),
    R("R9", "1k", "UART_RX_EXT", "UART_RX", "C21190", "0603WAF1001T5E", (350.52, 223.52),
      desc="series, Pi RXD; small so a device low stays < 0.2 V against R11 and the Pi pad pull-up"),
    R("R10", "1k", "GPIO17", "GPIO17_EXT", "C21190", "0603WAF1001T5E", (363.22, 223.52), desc="series, GPIO17"),
    R("R11", "100k", "+3V3", "UART_RX", "C25803", "0603WAF1003T5E", (312.42, 200.66),
      desc="RXD idle-high pull-up; must stay >> R9 (1k series)"),
    R("R12", "10k", "+3V3", "GPIO17", "C25804", "0603WAF1002T5E", (325.12, 200.66),
      desc="GPIO17 defined high level (beats the ~50k pad pull-down)"),
    dict(ref="U8", sym="Power_Protection:SRV05-4", value="SRV05-4",
         fp="SensorHAT:SOT-23-6_L2.9-W1.6-P0.95-LS2.8-BR",
         LCSC="C85364", MPN="SRV05-4-P-T7", Manufacturer="ProTek Devices",
         pins={"1": "ONEWIRE_EXT", "2": "GND", "3": "UART_TX_EXT", "4": "UART_RX_EXT", "5": "ESD_REF",
               "6": "GPIO17_EXT"},
         sch=(190.5, 238.76), desc="ESD protection for the external header signals"),
    R("R13", "100k", "+3V3", "ESD_REF", "C25803", "0603WAF1003T5E", (220.98, 231.14),
      desc="ESD reference via 100k (limits back-feed)"),
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    dict(ref="Q1", sym="Transistor_FET:AO3401A", value="AO3401A",
         fp="SensorHAT:SOT-23_L2.9-W1.3-P1.90-LS2.4-BR",
         LCSC="C15127", MPN="AO3401A", Manufacturer="Alpha & Omega",
         pins={"1": "Q1_G", "2": "+5V_FUSED", "3": "+5V_SW"}, sch=(269.24, 195.58),
         desc="High-side switch: switched 5 V only while a host (Pi or XIAO) is on"),
    dict(ref="Q2", sym="SensorHAT:AO3400A", value="AO3400A",
         fp="SensorHAT:SOT-23_L2.9-W1.3-P1.90-LS2.4-BR",
         LCSC="C20917", MPN="AO3400A", Manufacturer="Alpha & Omega",
         pins={"1": "LDO_EN", "2": "GND", "3": "Q2_D"}, sch=(266.7, 228.6),
         desc="Q1 gate driver (Vth max 1.45 V: LDO_EN is only ~2.7 V behind the BAV70)"),
    R("R15", "10k", "Q2_D", "Q1_G", "C25804", "0603WAF1002T5E", (284.48, 215.9), desc="Q1 gate series (soft start)"),
    C("C16", "100nF", "Q1_G", "+5V_SW", "C14663", "CC0603KRX7R9BB104", (297.18, 215.9), mfr="YAGEO",
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      desc="Q1 gate-source cap: keeps Q1 off while +5V ramps up (C16 alone would let +5V_SW follow)"),
    dict(ref="JP1", sym="Jumper:SolderJumper_2_Open", value="J3 VCC = 3V3",
         fp="Jumper:SolderJumper-2_P1.3mm_Open_RoundedPad1.0x1.5mm",
         pins={"1": "+3V3", "2": "UART_VCC"}, sch=(302.26, 172.72), no_bom=True,
         desc="Bridge for 3.3 V on J3 pin 1 (bridge JP1 OR JP3, never both)"),
    dict(ref="JP3", sym="Jumper:SolderJumper_2_Open", value="J3 VCC = 5V",
         fp="Jumper:SolderJumper-2_P1.3mm_Open_RoundedPad1.0x1.5mm",
         pins={"1": "+5V_SW", "2": "UART_VCC"}, sch=(302.26, 185.42), no_bom=True,
         desc="Bridge for switched, fused 5 V on J3 pin 1 (bridge JP1 OR JP3, never both)"),
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

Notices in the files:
scripts/design.py:
SPDX-FileCopyrightText: 2026 Emanuel Bachmann
SPDX-License-Identifier: CERN-OHL-S-2.0
